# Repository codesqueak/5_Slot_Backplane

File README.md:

# 5 Slot Backplane

A compact Backplane for Nascom / Gemini / 80-BUS Computers

## Introduction

A new design backplane for Nascom / Gemini / Other 80-BUS Systems

Features

* 5 Slots
* Full interrupt daisy-chaining
* Ground rails between all signals for reliability
* All signal lines clearly labelled
* Pads for Reset switch
* Pads for 5V power indicator
* Pads for Molex KK 396 power connector
* Size 21 x 10 cm (approximately)

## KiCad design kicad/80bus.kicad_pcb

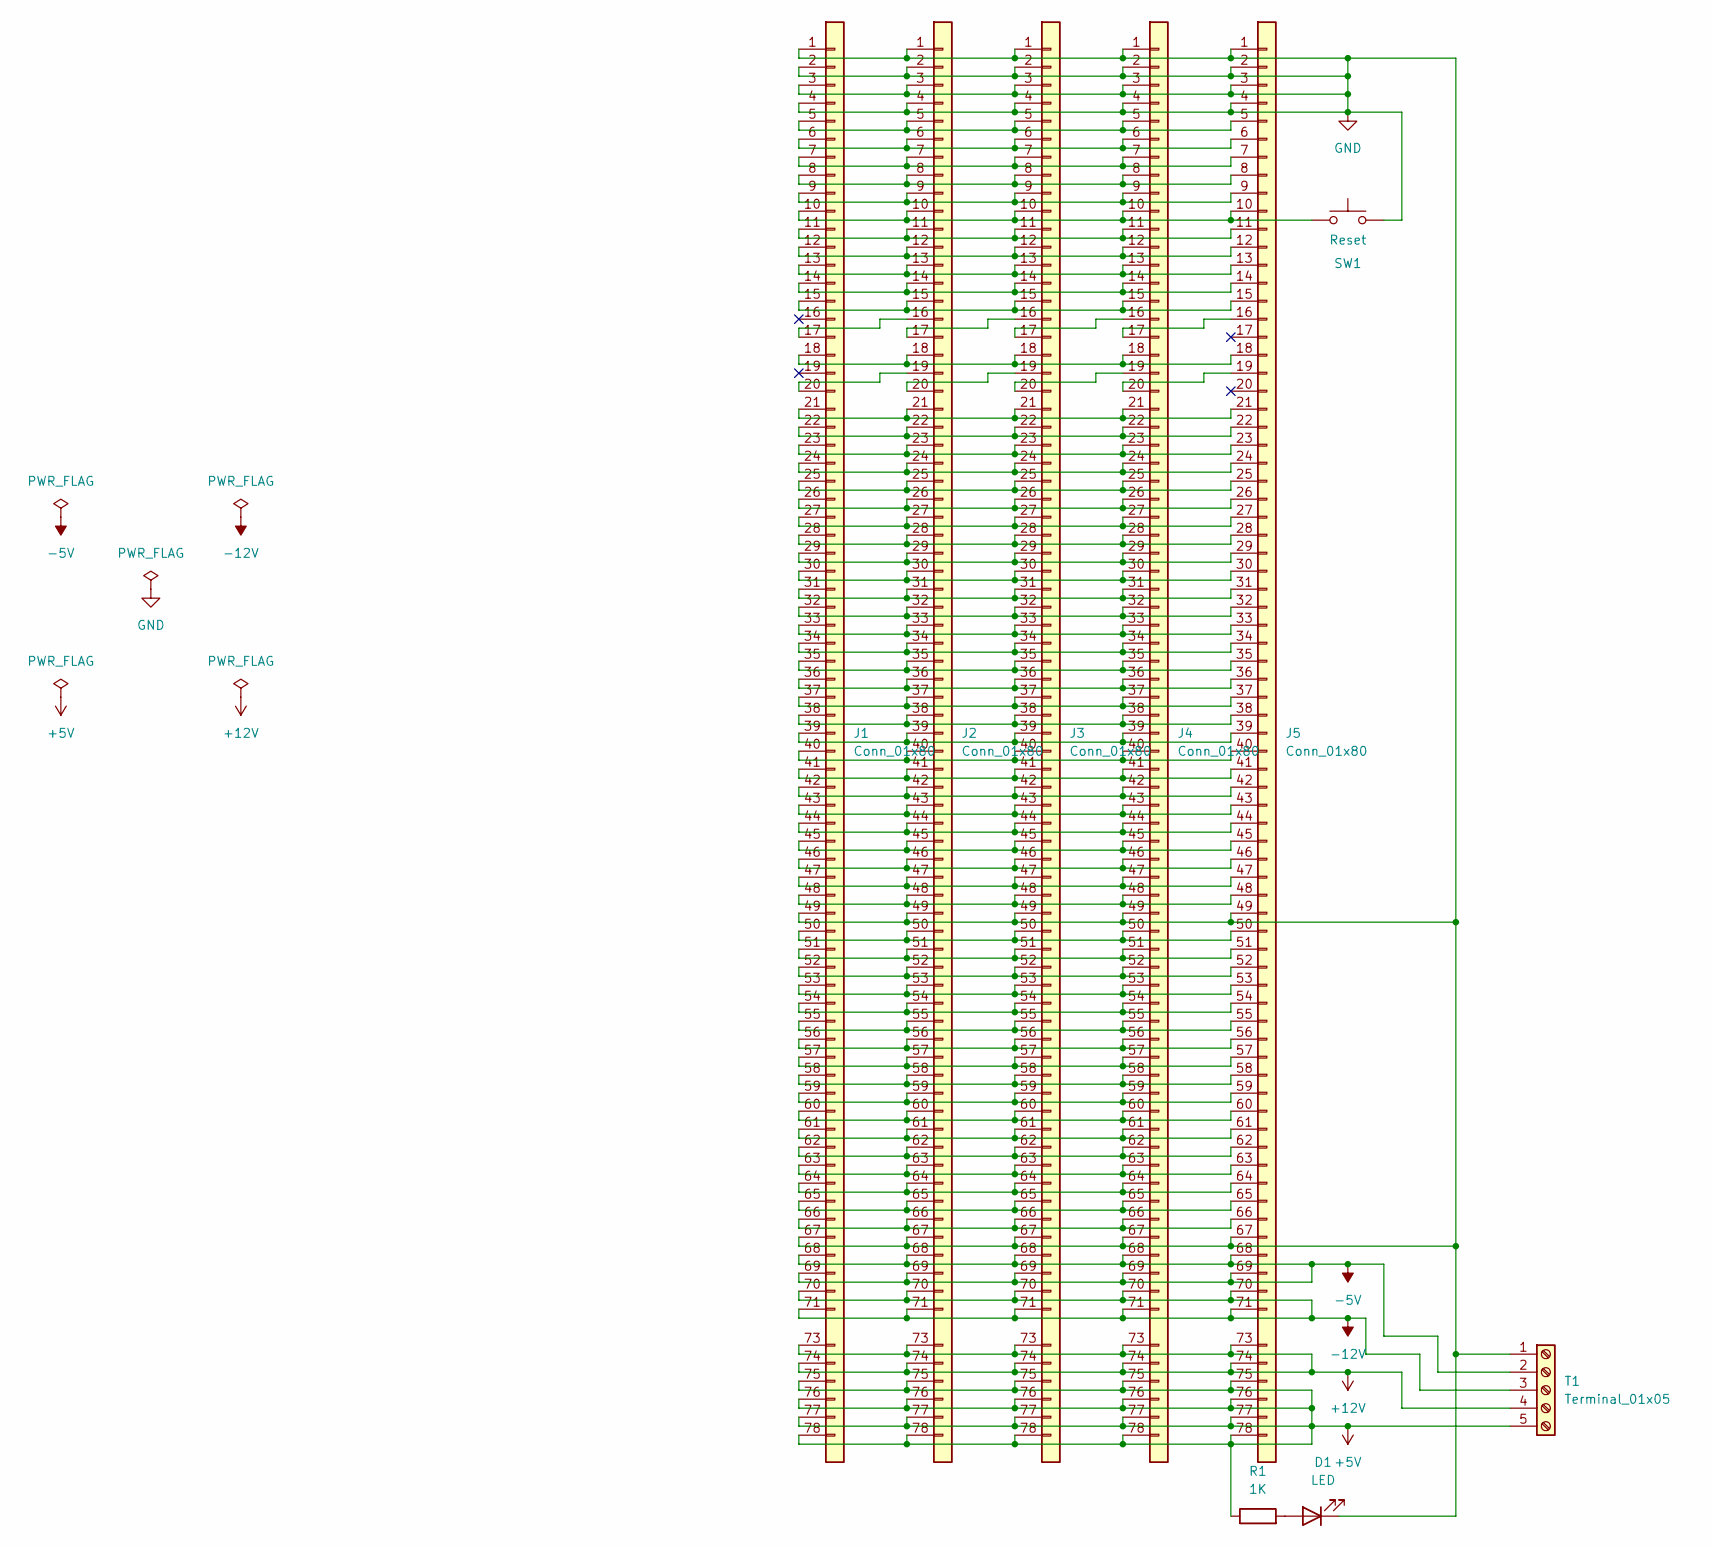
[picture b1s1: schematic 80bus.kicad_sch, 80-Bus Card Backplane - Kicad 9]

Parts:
D1: LED; LED_D3.0mm
J1, J2, J3, J4, J5: Conn_01x80; PinHeader_1x80_P2.54mm_Vertical
R1: 1K; R_Axial_DIN0309_L9.0mm_D3.2mm_P12.70mm_Horizontal
SW1: Reset; SW_PUSH_6mm_H5mm
T1: Terminal_01x05; Molex_KK-396_A-41791-0005_1x05_P3.96mm_Vertical

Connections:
+5V: J1.75 (Pin_35), J1.76 (Pin_36), J1.77 (Pin_37), J1.78 (Pin_38), J2.75 (Pin_35), J2.76 (Pin_36), J2.77 (Pin_37), J2.78 (Pin_38), J3.75 (Pin_35), J3.76 (Pin_36), J3.77 (Pin_37), J3.78 (Pin_38), J4.75 (Pin_35), J4.76 (Pin_36), J4.77 (Pin_37), J4.78 (Pin_38), J5.75 (Pin_35), J5.76 (Pin_36), J5.77 (Pin_37), J5.78 (Pin_38), R1.1, T1.5
+12V: J1.73 (Pin_33), J1.74 (Pin_34), J2.73 (Pin_33), J2.74 (Pin_34), J3.73 (Pin_33), J3.74 (Pin_34), J4.73 (Pin_33), J4.74 (Pin_34), J5.73 (Pin_33), J5.74 (Pin_34), T1.4
-5V: J1.68 (Pin_28), J1.69 (Pin_29), J2.68 (Pin_28), J2.69 (Pin_29), J3.68 (Pin_28), J3.69 (Pin_29), J4.68 (Pin_28), J4.69 (Pin_29), J5.68 (Pin_28), J5.69 (Pin_29), T1.2
-12V: J1.70 (Pin_30), J1.71 (Pin_31), J2.70 (Pin_30), J2.71 (Pin_31), J3.70 (Pin_30), J3.71 (Pin_31), J4.70 (Pin_30), J4.71 (Pin_31), J5.70 (Pin_30), J5.71 (Pin_31), T1.3
GND: D1.1 (K), J1.1, J1.2, J1.3, J1.4, J1.49 (Pin_9), J1.67 (Pin_27), J2.1, J2.2, J2.3, J2.4, J2.49 (Pin_9), J2.67 (Pin_27), J3.1, J3.2, J3.3, J3.4, J3.49 (Pin_9), J3.67 (Pin_27), J4.1, J4.2, J4.3, J4.4, J4.49 (Pin_9), J4.67 (Pin_27), J5.1, J5.2, J5.3, J5.4, J5.49 (Pin_9), J5.67 (Pin_27), SW1.2, T1.1
unnamed: D1.2 (A), R1.2
unnamed: J1.41 (Pin_1), J2.41 (Pin_1), J3.41 (Pin_1), J4.41 (Pin_1), J5.41 (Pin_1)
unnamed: J1.42 (Pin_2), J2.42 (Pin_2), J3.42 (Pin_2), J4.42 (Pin_2), J5.42 (Pin_2)
unnamed: J1.43 (Pin_3), J2.43 (Pin_3), J3.43 (Pin_3), J4.43 (Pin_3), J5.43 (Pin_3)
unnamed: J1.44 (Pin_4), J2.44 (Pin_4), J3.44 (Pin_4), J4.44 (Pin_4), J5.44 (Pin_4)
unnamed: J1.5, J2.5, J3.5, J4.5, J5.5
unnamed: J1.45 (Pin_5), J2.45 (Pin_5), J3.45 (Pin_5), J4.45 (Pin_5), J5.45 (Pin_5)
unnamed: J1.6, J2.6, J3.6, J4.6, J5.6
unnamed: J1.46 (Pin_6), J2.46 (Pin_6), J3.46 (Pin_6), J4.46 (Pin_6), J5.46 (Pin_6)
unnamed: J1.7, J2.7, J3.7, J4.7, J5.7
unnamed: J1.47 (Pin_7), J2.47 (Pin_7), J3.47 (Pin_7), J4.47 (Pin_7), J5.47 (Pin_7)
unnamed: J1.8, J2.8, J3.8, J4.8, J5.8
unnamed: J1.48 (Pin_8), J2.48 (Pin_8), J3.48 (Pin_8), J4.48 (Pin_8), J5.48 (Pin_8)
unnamed: J1.9, J2.9, J3.9, J4.9, J5.9
unnamed: J1.10, J2.10, J3.10, J4.10, J5.10, SW1.1
unnamed: J1.50 (Pin_10), J2.50 (Pin_10), J3.50 (Pin_10), J4.50 (Pin_10), J5.50 (Pin_10)
unnamed: J1.11, J2.11, J3.11, J4.11, J5.11
unnamed: J1.51 (Pin_11), J2.51 (Pin_11), J3.51 (Pin_11), J4.51 (Pin_11), J5.51 (Pin_11)
unnamed: J1.12, J2.12, J3.12, J4.12, J5.12
unnamed: J1.52 (Pin_12), J2.52 (Pin_12), J3.52 (Pin_12), J4.52 (Pin_12), J5.52 (Pin_12)
unnamed: J1.13, J2.13, J3.13, J4.13, J5.13
unnamed: J1.53 (Pin_13), J2.53 (Pin_13), J3.53 (Pin_13), J4.53 (Pin_13), J5.53 (Pin_13)
unnamed: J1.14, J2.14, J3.14, J4.14, J5.14
unnamed: J1.54 (Pin_14), J2.54 (Pin_14), J3.54 (Pin_14), J4.54 (Pin_14), J5.54 (Pin_14)
unnamed: J1.15, J2.15, J3.15, J4.15, J5.15
unnamed: J1.55 (Pin_15), J2.55 (Pin_15), J3.55 (Pin_15), J4.55 (Pin_15), J5.55 (Pin_15)
unnamed: J1.56 (Pin_16), J2.56 (Pin_16), J3.56 (Pin_16), J4.56 (Pin_16), J5.56 (Pin_16)
unnamed: J1.17, J2.16
unnamed: J1.57 (Pin_17), J2.57 (Pin_17), J3.57 (Pin_17), J4.57 (Pin_17), J5.57 (Pin_17)
unnamed: J1.18, J2.18, J3.18, J4.18, J5.18
unnamed: J1.58 (Pin_18), J2.58 (Pin_18), J3.58 (Pin_18), J4.58 (Pin_18), J5.58 (Pin_18)
unnamed: J1.59 (Pin_19), J2.59 (Pin_19), J3.59 (Pin_19), J4.59 (Pin_19), J5.59 (Pin_19)
unnamed: J1.20, J2.19
unnamed: J1.60 (Pin_20), J2.60 (Pin_20), J3.60 (Pin_20), J4.60 (Pin_20), J5.60 (Pin_20)
unnamed: J1.21, J2.21, J3.21, J4.21, J5.21
unnamed: J1.61 (Pin_21), J2.61 (Pin_21), J3.61 (Pin_21), J4.61 (Pin_21), J5.61 (Pin_21)
unnamed: J1.22, J2.22, J3.22, J4.22, J5.22
unnamed: J1.62 (Pin_22), J2.62 (Pin_22), J3.62 (Pin_22), J4.62 (Pin_22), J5.62 (Pin_22)
unnamed: J1.23, J2.23, J3.23, J4.23, J5.23
unnamed: J1.63 (Pin_23), J2.63 (Pin_23), J3.63 (Pin_23), J4.63 (Pin_23), J5.63 (Pin_23)
unnamed: J1.24, J2.24, J3.24, J4.24, J5.24
unnamed: J1.64 (Pin_24), J2.64 (Pin_24), J3.64 (Pin_24), J4.64 (Pin_24), J5.64 (Pin_24)
unnamed: J1.25, J2.25, J3.25, J4.25, J5.25
unnamed: J1.65 (Pin_25), J2.65 (Pin_25), J3.65 (Pin_25), J4.65 (Pin_25), J5.65 (Pin_25)
unnamed: J1.26, J2.26, J3.26, J4.26, J5.26
unnamed: J1.66 (Pin_26), J2.66 (Pin_26), J3.66 (Pin_26), J4.66 (Pin_26), J5.66 (Pin_26)
unnamed: J1.27, J2.27, J3.27, J4.27, J5.27
unnamed: J1.28, J2.28, J3.28, J4.28, J5.28
unnamed: J1.29, J2.29, J3.29, J4.29, J5.29
unnamed: J1.30, J2.30, J3.30, J4.30, J5.30
unnamed: J1.31, J2.31, J3.31, J4.31, J5.31
unnamed: J1.32, J2.32, J3.32, J4.32, J5.32
unnamed: J1.33, J2.33, J3.33, J4.33, J5.33
unnamed: J1.34, J2.34, J3.34, J4.34, J5.34
unnamed: J1.35, J2.35, J3.35, J4.35, J5.35
unnamed: J1.36, J2.36, J3.36, J4.36, J5.36
unnamed: J1.37, J2.37, J3.37, J4.37, J5.37
unnamed: J1.38, J2.38, J3.38, J4.38, J5.38
unnamed: J1.39, J2.39, J3.39, J4.39, J5.39
unnamed: J1.40, J2.40, J3.40, J4.40, J5.40
unnamed: J2.17, J3.16
unnamed: J2.20, J3.19
unnamed: J3.17, J4.16
unnamed: J3.20, J4.19
unnamed: J4.17, J5.16
unnamed: J4.20, J5.19

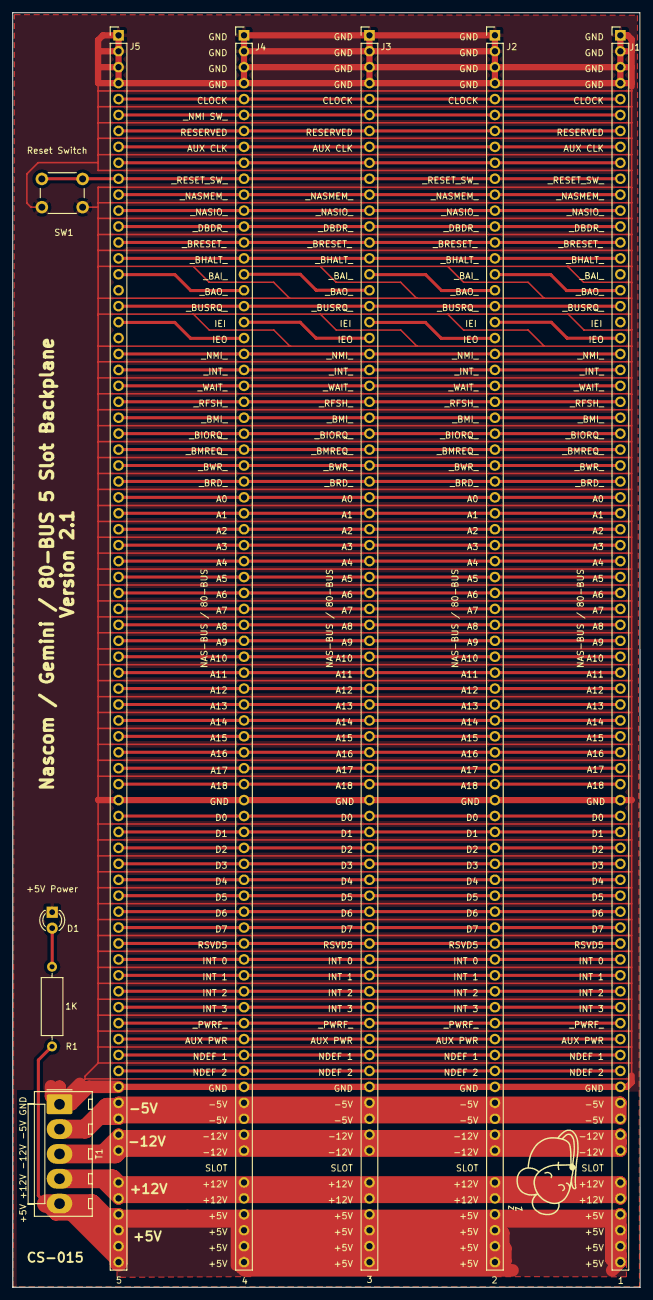
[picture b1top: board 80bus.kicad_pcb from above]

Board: 2 copper layers, 100.0 x 203.2 mm, 11 parts (1 on the bottom side), 71 nets.

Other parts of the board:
G1: LOGO; sleepymouse_very_small
G001: LOGO; qr code

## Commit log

2023-06-25 Initial file upload
2023-06-25 Board image
2023-06-25 Missing .ignore file
2023-06-25 Tweak README
2025-04-23 Kicad 9 and docs
2025-04-23 docs
